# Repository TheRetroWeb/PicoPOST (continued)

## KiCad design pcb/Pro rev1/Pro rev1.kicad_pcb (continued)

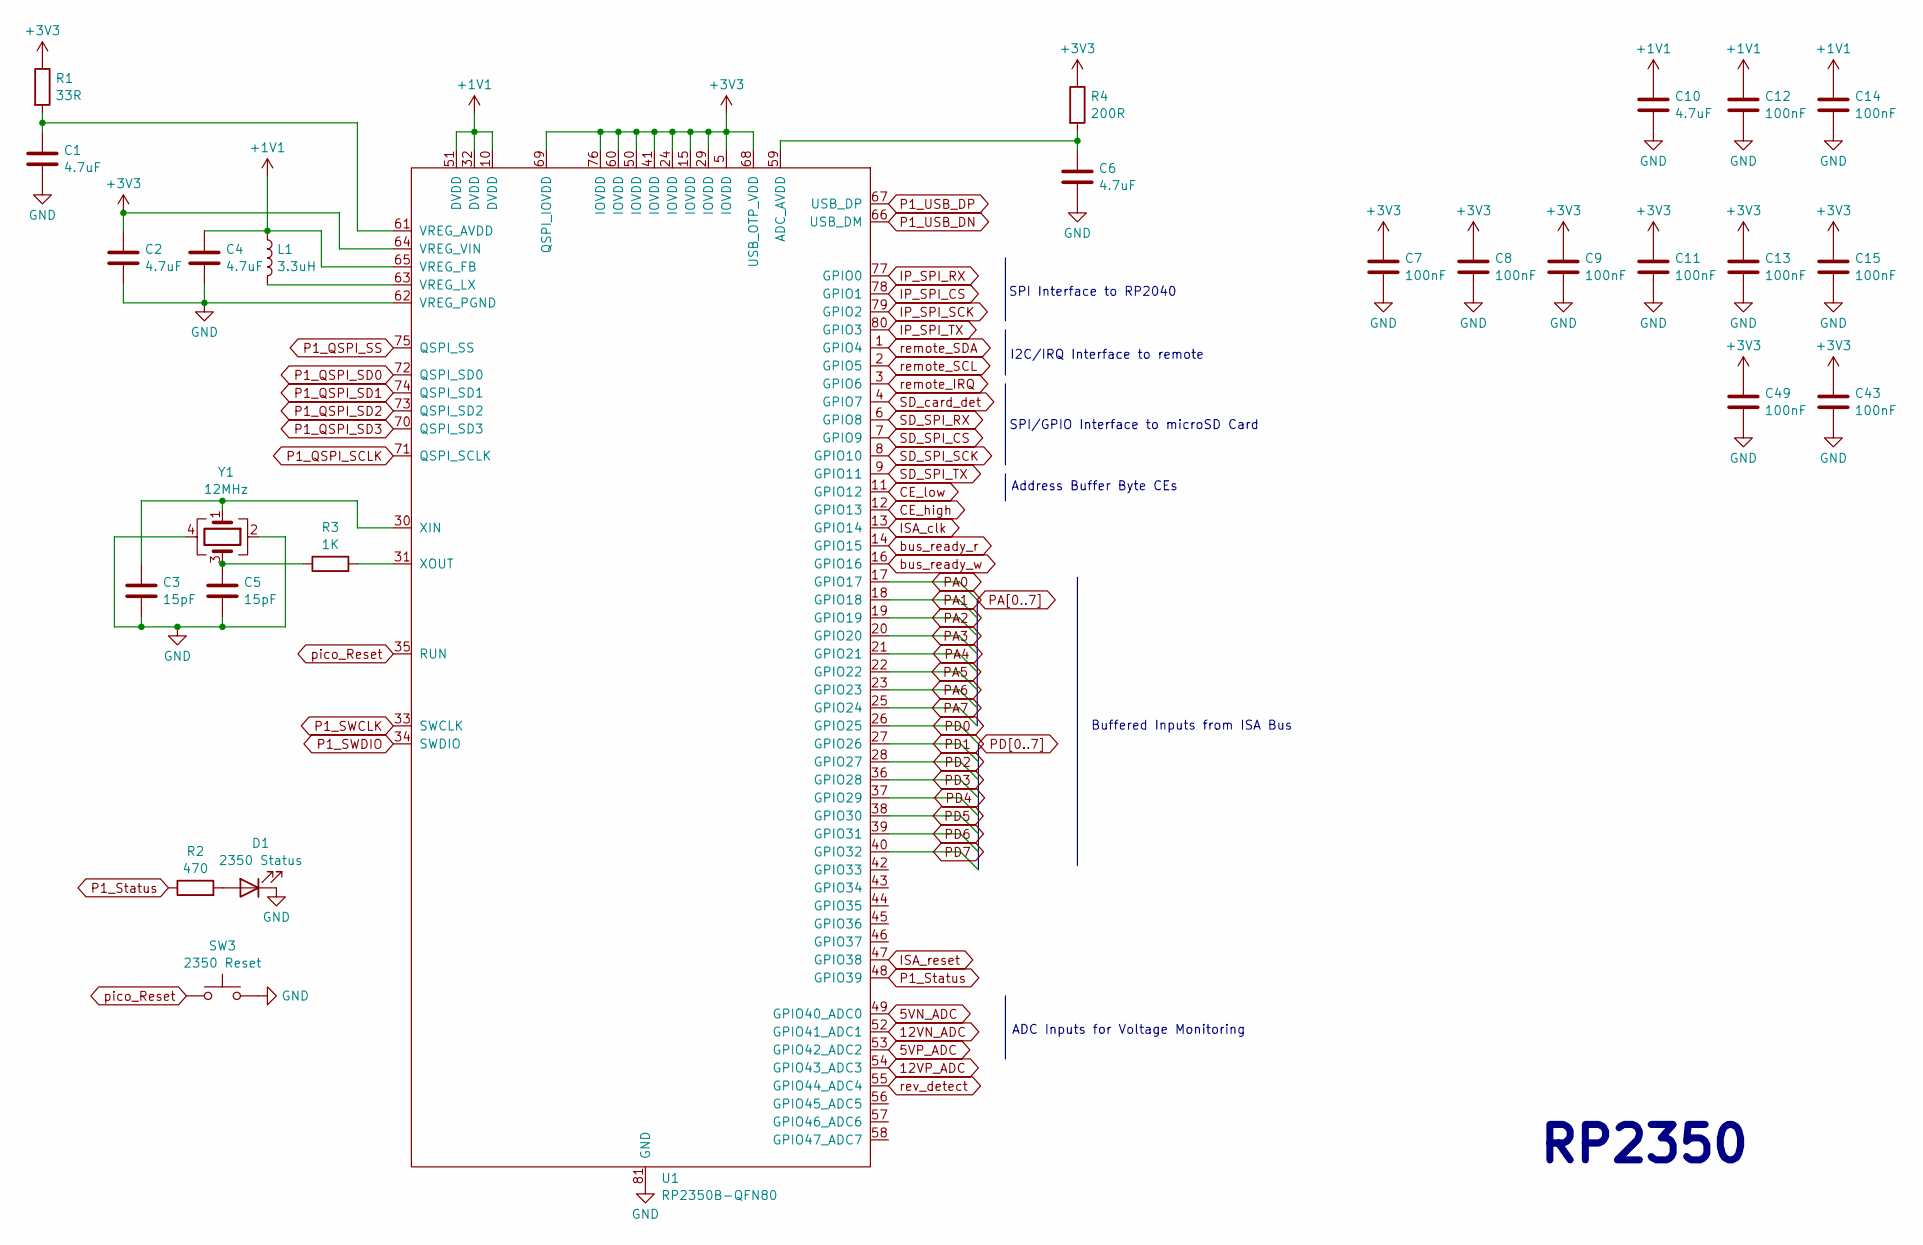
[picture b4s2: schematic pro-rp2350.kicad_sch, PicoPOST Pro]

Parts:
C1, C2, C4: 4.7uF; C_0402_1005Metric
C3, C5: 15pF; C_0402_1005Metric
C6, C10: 4.7uF; C_0603_1608Metric
C7, C8, C9, C11, C12, C13, C14, C15, C43, C49: 100nF; C_0402_1005Metric
D1: 2350 Status; LED_0805_2012Metric
L1: 3.3uH; L_Murata_DFE201610P
R1: 33R; R_0402_1005Metric
R2: 470; R_0603_1608Metric
R3: 1K; R_0402_1005Metric
R4: 200R; R_0402_1005Metric
SW3: 2350 Reset; SW_SPST_TS-1088-xR020
U1: RP2350B-QFN80; RP2350B_QFN-80_EP_10.573x10.573_Pitch0.4mm
Y1: 12MHz; Crystal_SMD_Abracon_ABM8G-4Pin_3.2x2.5mm

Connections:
5VN_ADC: U1.49 (GPIO40_ADC0); also elsewhere on the board
5VP_ADC: U1.53 (GPIO42_ADC2); also elsewhere on the board
12VN_ADC: U1.52 (GPIO41_ADC1); also elsewhere on the board
12VP_ADC: U1.54 (GPIO43_ADC3); also elsewhere on the board
+1V1: C4.1, C10.1, C12.1, C14.1, L1.1, U1.10 (DVDD), U1.32 (DVDD), U1.51 (DVDD), U1.65 (VREG_FB)
+3V3: C2.1, C7.1, C8.1, C9.1, C11.1, C13.1, C15.1, C43.1, C49.1, R1.1, R4.1, U1.5 (IOVDD), U1.15 (IOVDD), U1.24 (IOVDD), U1.29 (IOVDD), U1.41 (IOVDD), U1.50 (IOVDD), U1.60 (IOVDD), U1.64 (VREG_VIN), U1.68 (USB_OTP_VDD), U1.69 (QSPI_IOVDD), U1.76 (IOVDD); also elsewhere on the board
CE_high: U1.12 (GPIO13); also elsewhere on the board
CE_low: U1.11 (GPIO12); also elsewhere on the board
GND: C1.2, C2.2, C3.1, C4.2, C5.2, C6.2, C7.2, C8.2, C9.2, C10.2, C11.2, C12.2, C13.2, C14.2, C15.2, C43.2, C49.2, D1.1 (K), SW3.2, U1.62 (VREG_PGND), U1.81 (GND), Y1.2, Y1.4; also elsewhere on the board
IP_SPI_CS: U1.78 (GPIO1); also elsewhere on the board
IP_SPI_RX: U1.77 (GPIO0); also elsewhere on the board
IP_SPI_SCK: U1.79 (GPIO2); also elsewhere on the board
IP_SPI_TX: U1.80 (GPIO3); also elsewhere on the board
ISA_clk: U1.13 (GPIO14); also elsewhere on the board
ISA_reset: U1.47 (GPIO38); also elsewhere on the board
unnamed: C5.1, R3.1, Y1.3
unnamed: D1.2 (A), R2.2
unnamed: C6.1, R4.2, U1.59 (ADC_AVDD)
unnamed: C1.1, R1.2, U1.61 (VREG_AVDD)
unnamed: L1.2, U1.63 (VREG_LX)
unnamed: C3.2, U1.30 (XIN), Y1.1
unnamed: R3.2, U1.31 (XOUT)
P1_QSPI_SCLK: U1.71 (QSPI_SCLK); also elsewhere on the board
P1_QSPI_SD0: U1.72 (QSPI_SD0); also elsewhere on the board
P1_QSPI_SD1: U1.74 (QSPI_SD1); also elsewhere on the board
P1_QSPI_SD2: U1.73 (QSPI_SD2); also elsewhere on the board
P1_QSPI_SD3: U1.70 (QSPI_SD3); also elsewhere on the board
P1_QSPI_SS: U1.75 (QSPI_SS); also elsewhere on the board
P1_SWCLK: U1.33 (SWCLK); also elsewhere on the board
P1_SWDIO: U1.34 (SWDIO); also elsewhere on the board
P1_Status: R2.1, U1.48 (GPIO39)
P1_USB_DN: U1.66 (USB_DM); also elsewhere on the board
P1_USB_DP: U1.67 (USB_DP); also elsewhere on the board
PA0: U1.17 (GPIO17); also elsewhere on the board
PA1: U1.18 (GPIO18); also elsewhere on the board
PA2: U1.19 (GPIO19); also elsewhere on the board
PA3: U1.20 (GPIO20); also elsewhere on the board
PA4: U1.21 (GPIO21); also elsewhere on the board
PA5: U1.22 (GPIO22); also elsewhere on the board
PA6: U1.23 (GPIO23); also elsewhere on the board
PA7: U1.25 (GPIO24); also elsewhere on the board
PD0: U1.26 (GPIO25); also elsewhere on the board
PD1: U1.27 (GPIO26); also elsewhere on the board
PD2: U1.28 (GPIO27); also elsewhere on the board
PD3: U1.36 (GPIO28); also elsewhere on the board
PD4: U1.37 (GPIO29); also elsewhere on the board
PD5: U1.38 (GPIO30); also elsewhere on the board
PD6: U1.39 (GPIO31); also elsewhere on the board
PD7: U1.40 (GPIO32); also elsewhere on the board
SD_SPI_CS: U1.7 (GPIO9); also elsewhere on the board
SD_SPI_RX: U1.6 (GPIO8); also elsewhere on the board
SD_SPI_SCK: U1.8 (GPIO10); also elsewhere on the board
SD_SPI_TX: U1.9 (GPIO11); also elsewhere on the board
SD_card_det: U1.4 (GPIO7); also elsewhere on the board
bus_ready_r: U1.14 (GPIO15); also elsewhere on the board
bus_ready_w: U1.16 (GPIO16); also elsewhere on the board
pico_Reset: SW3.1, U1.35 (RUN)
remote_IRQ: U1.3 (GPIO6); also elsewhere on the board
remote_SCL: U1.2 (GPIO5); also elsewhere on the board
remote_SDA: U1.1 (GPIO4); also elsewhere on the board
rev_detect: U1.55 (GPIO44_ADC4); also elsewhere on the board

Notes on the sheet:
SPI/GPIO Interface to microSD Card
I2C/IRQ Interface to remote
Buffered Inputs from ISA Bus
SPI Interface to RP2040
Address Buffer Byte CEs
ADC Inputs for Voltage Monitoring
RP2350

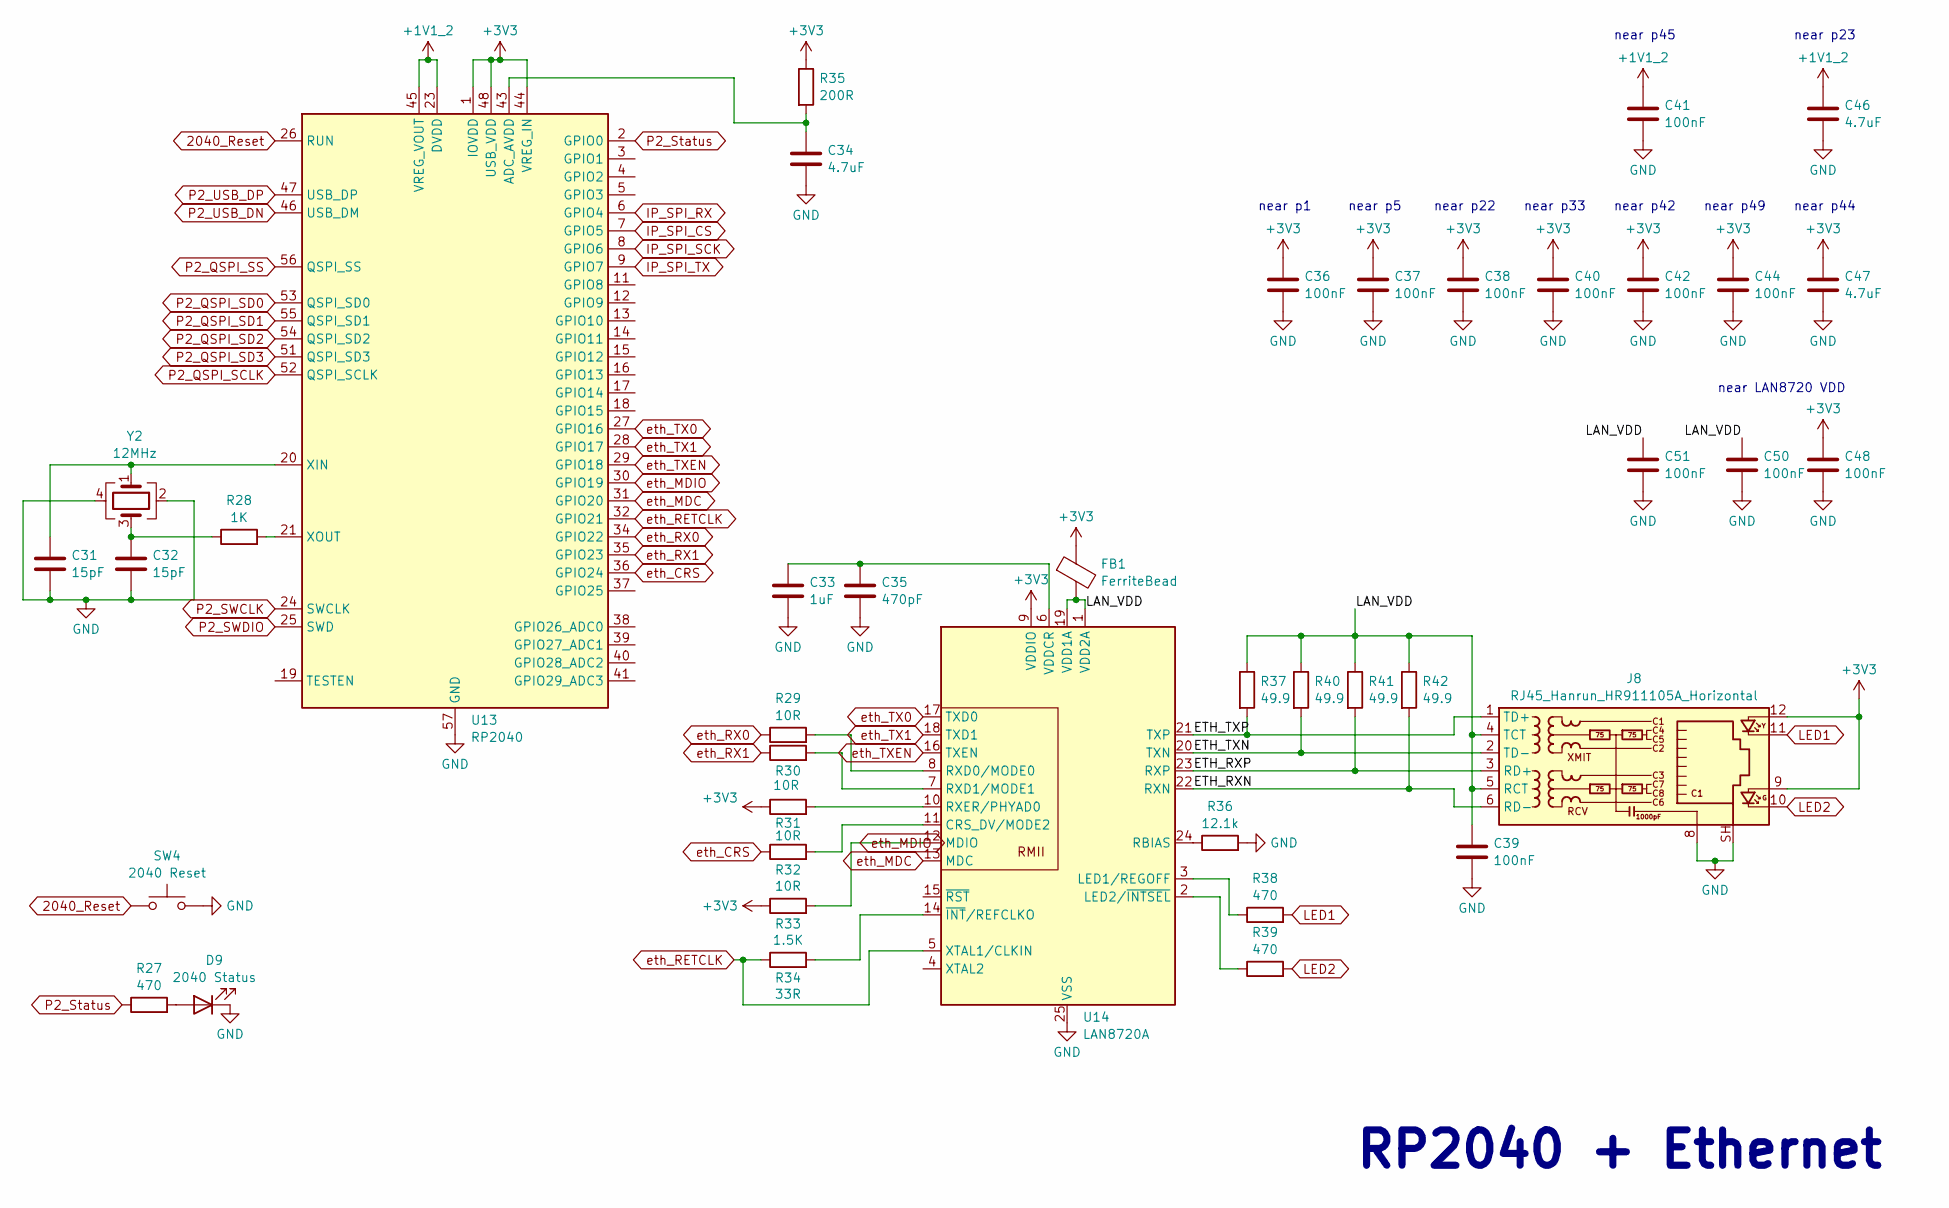
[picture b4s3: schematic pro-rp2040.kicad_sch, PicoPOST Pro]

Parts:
C31, C32: 15pF; C_0402_1005Metric
C33: 1uF; C_0603_1608Metric
C34, C46, C47: 4.7uF; C_0603_1608Metric
C35: 470pF; C_0603_1608Metric
C36, C37, C38, C39, C40, C41, C42, C44, C48, C50, C51: 100nF; C_0402_1005Metric
D9: 2040 Status; LED_0805_2012Metric
FB1: FerriteBead; L_0603_1608Metric
J8: RJ45_Hanrun_HR911105A_Horizontal
R27, R38, R39: 470; R_0603_1608Metric
R28: 1K; R_0402_1005Metric
R29, R30, R31, R32: 10R; R_0402_1005Metric
R33: 1.5K; R_0402_1005Metric
R34: 33R; R_0402_1005Metric
R35: 200R; R_0402_1005Metric
R36: 12.1k; R_0402_1005Metric
R37, R40, R41, R42: 49.9; R_0603_1608Metric
SW4: 2040 Reset; SW_SPST_TS-1088-xR020
U13: RP2040; QFN-56-1EP_7x7mm_P0.4mm_EP3.2x3.2mm
U14: LAN8720A; VQFN-24-1EP_4x4mm_P0.5mm_EP2.5x2.5mm_ThermalVias
Y2: 12MHz; Crystal_SMD_Abracon_ABM8G-4Pin_3.2x2.5mm

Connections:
2040_Reset: SW4.1, U13.26 (RUN)
+1V1_2: C41.1, C46.1, U13.23 (DVDD), U13.45 (VREG_VOUT), U13.50 (DVDD)
+3V3: C36.1, C37.1, C38.1, C40.1, C42.1, C44.1, C47.1, C48.1, FB1.1, J8.9, J8.12, R31.1, R33.1, R35.1, U13.1 (IOVDD), U13.10 (IOVDD), U13.22 (IOVDD), U13.33 (IOVDD), U13.42 (IOVDD), U13.44 (VREG_IN), U13.48 (USB_VDD), U13.49 (IOVDD), U14.9 (VDDIO); also elsewhere on the board
/RP2040/ETH_RXN: J8.6 (RD-), R42.2, U14.22 (RXN)
/RP2040/ETH_RXP: J8.3 (RD+), R41.2, U14.23 (RXP)
/RP2040/ETH_TXN: J8.2 (TD-), R40.2, U14.20 (TXN)
/RP2040/ETH_TXP: J8.1 (TD+), R37.2, U14.21 (TXP)
/RP2040/LAN_VDD: C39.1, C50.1, C51.1, FB1.2, J8.4 (TCT), J8.5 (RCT), R37.1, R40.1, R41.1, R42.1, U14.1 (VDD2A), U14.19 (VDD1A)
GND: C31.1, C32.2, C33.2, C34.2, C35.2, C36.2, C37.2, C38.2, C39.2, C40.2, C41.2, C42.2, C44.2, C46.2, C47.2, C48.2, C50.2, C51.2, D9.1 (K), J8.8, J8.SH, R36.2, SW4.2, U13.57 (GND), U14.25 (VSS), Y2.2, Y2.4; also elsewhere on the board
IP_SPI_CS: U13.7 (GPIO5); also elsewhere on the board
IP_SPI_RX: U13.6 (GPIO4); also elsewhere on the board
IP_SPI_SCK: U13.8 (GPIO6); also elsewhere on the board
IP_SPI_TX: U13.9 (GPIO7); also elsewhere on the board
LED1: J8.11, R38.2
LED2: J8.10, R39.2
unnamed: C32.1, R28.1, Y2.3
unnamed: D9.2 (A), R27.2
unnamed: C34.1, R35.2, U13.43 (ADC_AVDD)
unnamed: C31.2, U13.20 (XIN), Y2.1
unnamed: R28.2, U13.21 (XOUT)
unnamed: R32.2, U14.11 (CRS_DV/MODE2)
unnamed: R38.1, U14.3 (LED1/REGOFF)
unnamed: R39.1, U14.2 (LED2/~INTSEL)
unnamed: R36.1, U14.24 (RBIAS)
unnamed: R29.2, U14.8 (RXD0/MODE0)
unnamed: R30.2, U14.7 (RXD1/MODE1)
unnamed: R31.2, U14.10 (RXER/PHYAD0)
unnamed: C33.1, C35.1, U14.6 (VDDCR)
unnamed: R34.2, U14.14 (~INT/REFCLKO)
P2_QSPI_SCLK: U13.52 (QSPI_SCLK); also elsewhere on the board
P2_QSPI_SD0: U13.53 (QSPI_SD0); also elsewhere on the board
P2_QSPI_SD1: U13.55 (QSPI_SD1); also elsewhere on the board
P2_QSPI_SD2: U13.54 (QSPI_SD2); also elsewhere on the board
P2_QSPI_SD3: U13.51 (QSPI_SD3); also elsewhere on the board
P2_QSPI_SS: U13.56 (QSPI_SS); also elsewhere on the board
P2_SWCLK: U13.24 (SWCLK); also elsewhere on the board
P2_SWDIO: U13.25 (SWD); also elsewhere on the board
P2_Status: R27.1, U13.2 (GPIO0)
P2_USB_DN: U13.46 (USB_DM); also elsewhere on the board
P2_USB_DP: U13.47 (USB_DP); also elsewhere on the board
eth_CRS: R32.1, U13.36 (GPIO24)
eth_MDC: U13.31 (GPIO20), U14.13 (MDC)
eth_MDIO: R33.2, U13.30 (GPIO19), U14.12 (MDIO)
eth_RETCLK: R34.1, U13.32 (GPIO21), U14.5 (XTAL1/CLKIN)
eth_RX0: R29.1, U13.34 (GPIO22)
eth_RX1: R30.1, U13.35 (GPIO23)
eth_TX0: U13.27 (GPIO16), U14.17 (TXD0)
eth_TX1: U13.28 (GPIO17), U14.18 (TXD1)
eth_TXEN: U13.29 (GPIO18), U14.16 (TXEN)

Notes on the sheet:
near p42
near p5
near p44
near p22
near LAN8720 VDD
near p1
near p49
near p45
near p23
near p33
RP2040 + Ethernet

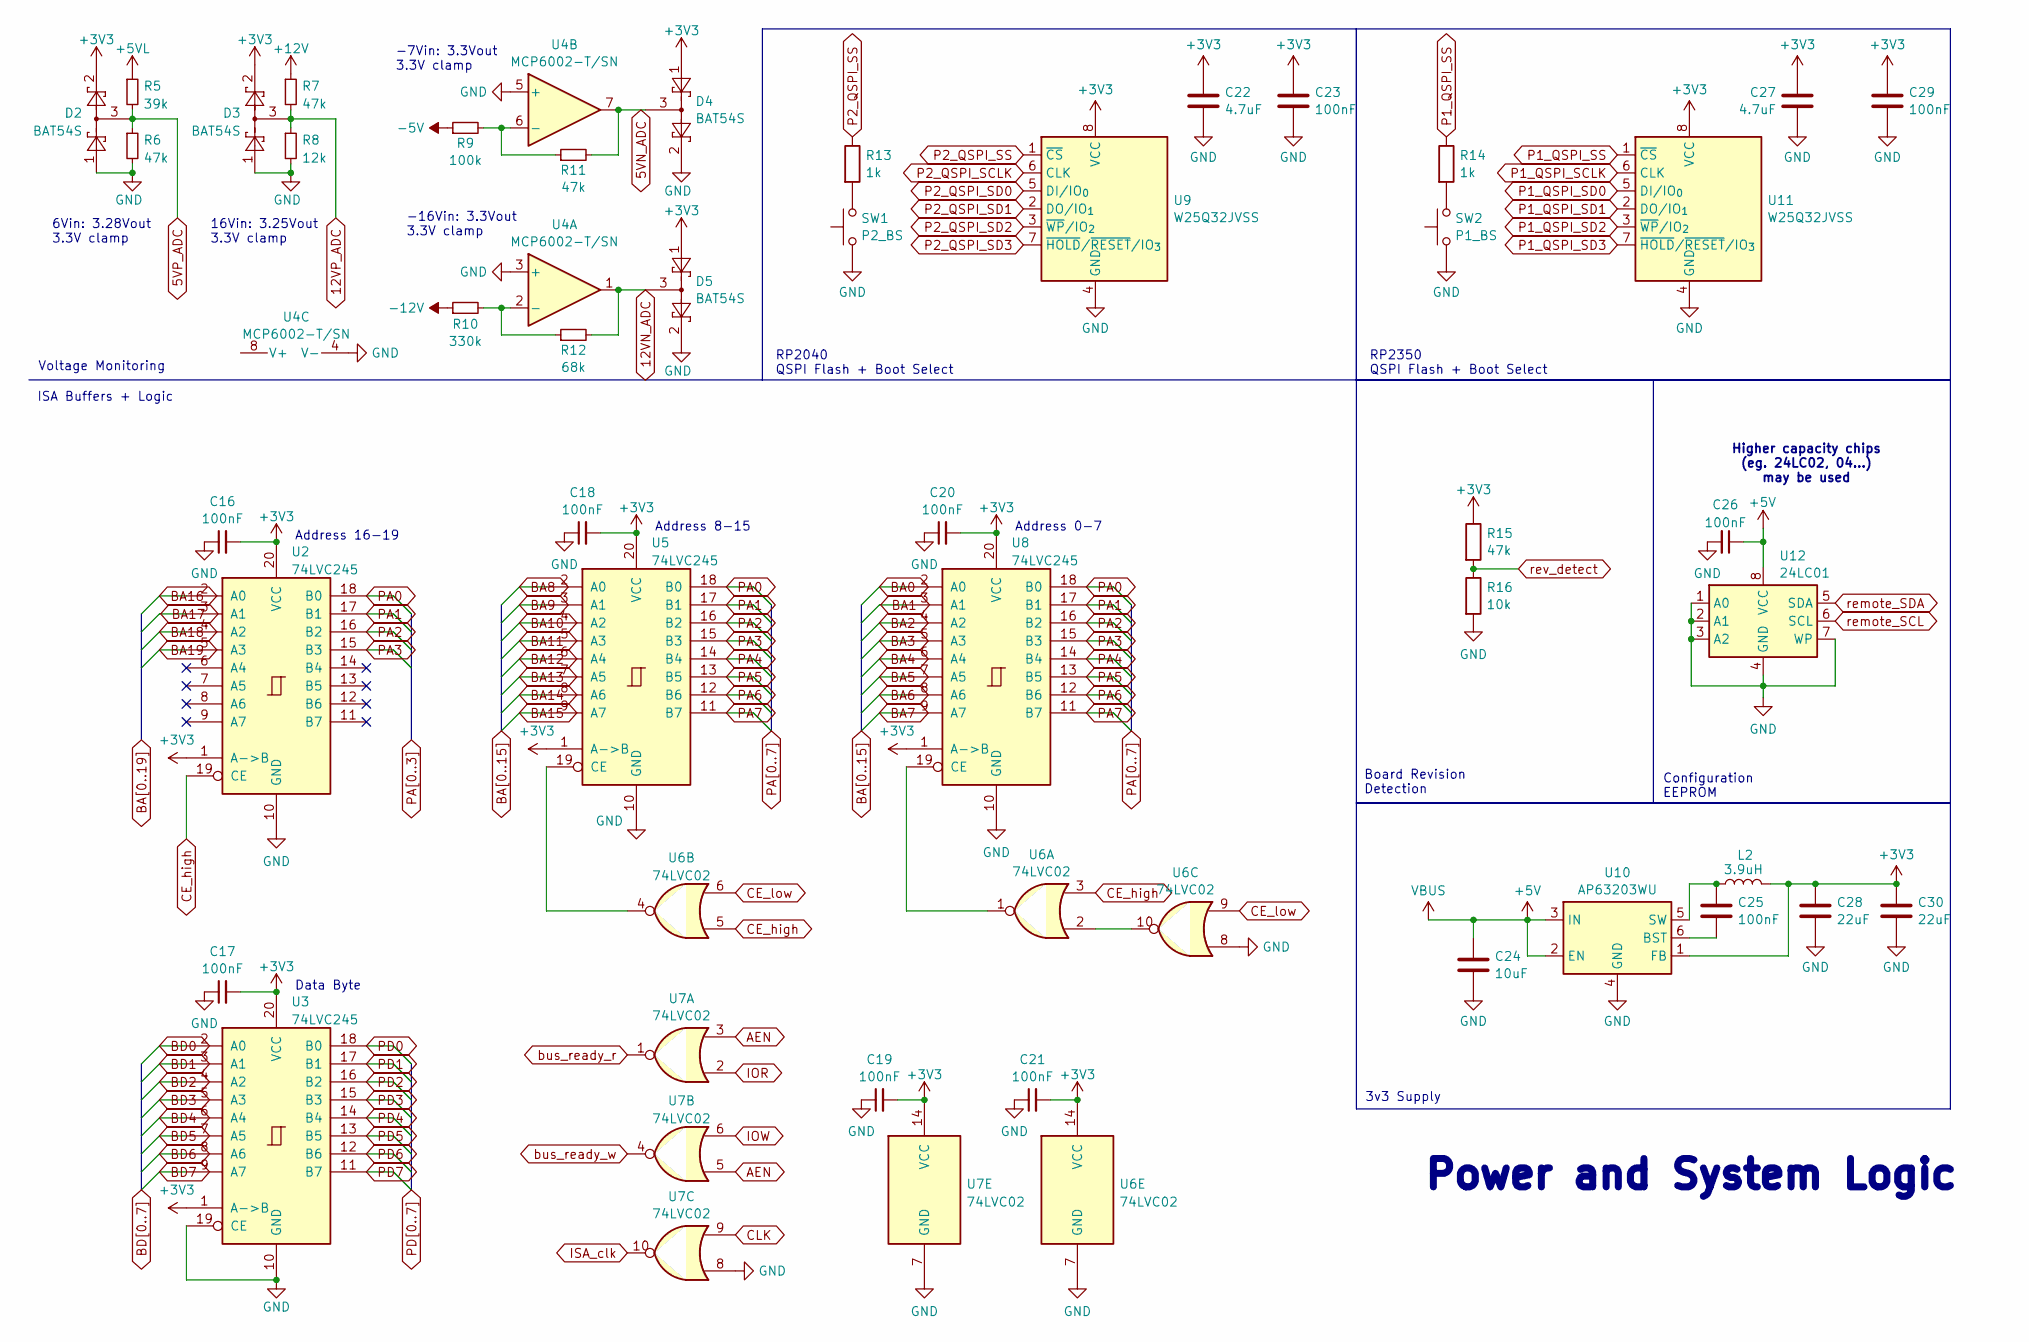
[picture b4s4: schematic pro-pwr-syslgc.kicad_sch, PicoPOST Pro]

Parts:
C16, C17, C18, C19, C20, C21, C23, C25, C26, C29: 100nF; C_0402_1005Metric
C22, C27: 4.7uF; C_0603_1608Metric
C24: 10uF; C_0805_2012Metric
C28, C30: 22uF; C_1206_3216Metric
D2, D3, D4, D5: BAT54S; SOT-23_Handsoldering
L2: 3.9uH; L_APV_ANR4030
R5: 39k; R_0603_1608Metric
R6, R7, R11, R15: 47k; R_0603_1608Metric
R8: 12k; R_0603_1608Metric
R9: 100k; R_0603_1608Metric
R10: 330k; R_0603_1608Metric
R12: 68k; R_0603_1608Metric
R13, R14: 1k; R_0603_1608Metric
R16: 10k; R_0603_1608Metric
SW1: P2_BS; SW_SPST_TS-1088-xR020
SW2: P1_BS; SW_SPST_TS-1088-xR020
U2, U3, U5, U8: 74LVC245; TSSOP-20_4.4x6.5mm_P0.65mm
U4: MCP6002-T/SN; SOIC-8_3.9x4.9mm_P1.27mm
U6, U7: 74LVC02; TSSOP-14_4.4x5mm_P0.65mm
U9, U11: W25Q32JVSS; SOIC-8_5.3x5.3mm_P1.27mm
U10: AP63203WU; TSOT-23-6
U12: 24LC01; SOIC-8_3.9x4.9mm_P1.27mm

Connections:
5VN_ADC: D4.3, R11.2, U4.7; also elsewhere on the board
5VP_ADC: D2.3, R5.2, R6.1; also elsewhere on the board
12VN_ADC: D5.3, R12.2, U4.1; also elsewhere on the board
12VP_ADC: D3.3, R7.2, R8.1; also elsewhere on the board
+3V3: C16.2, C17.2, C18.2, C19.2, C20.2, C21.2, C22.1, C23.1, C27.1, C28.1, C29.1, C30.1, D2.2, D3.2, D4.1, D5.1, L2.2, R15.1, U2.1 (A->B), U2.20 (VCC), U3.1 (A->B), U3.20 (VCC), U5.1 (A->B), U5.20 (VCC), U6.14 (VCC), U7.14 (VCC), U8.1 (A->B), U8.20 (VCC), U9.8 (VCC), U10.1 (FB), U11.8 (VCC); also elsewhere on the board
+5V: C24.1, C26.1, U10.2 (EN), U10.3 (IN), U12.8 (VCC); also elsewhere on the board
+5VL: R5.1; also elsewhere on the board
+12V: R7.1; also elsewhere on the board
-5V: R9.1; also elsewhere on the board
-12V: R10.1; also elsewhere on the board
AEN: U7.3, U7.5; also elsewhere on the board
BA0: U8.2 (A0); also elsewhere on the board
BA1: U8.3 (A1); also elsewhere on the board
BA2: U8.4 (A2); also elsewhere on the board
BA3: U8.5 (A3); also elsewhere on the board
BA4: U8.6 (A4); also elsewhere on the board
BA5: U8.7 (A5); also elsewhere on the board
BA6: U8.8 (A6); also elsewhere on the board
BA7: U8.9 (A7); also elsewhere on the board
BA8: U5.2 (A0); also elsewhere on the board
BA9: U5.3 (A1); also elsewhere on the board
BA10: U5.4 (A2); also elsewhere on the board
BA11: U5.5 (A3); also elsewhere on the board
BA12: U5.6 (A4); also elsewhere on the board
BA13: U5.7 (A5); also elsewhere on the board
BA14: U5.8 (A6); also elsewhere on the board
BA15: U5.9 (A7); also elsewhere on the board
BA16: U2.2 (A0); also elsewhere on the board
BA17: U2.3 (A1); also elsewhere on the board
BA18: U2.4 (A2); also elsewhere on the board
BA19: U2.5 (A3); also elsewhere on the board
BD0: U3.2 (A0); also elsewhere on the board
BD1: U3.3 (A1); also elsewhere on the board
BD2: U3.4 (A2); also elsewhere on the board
BD3: U3.5 (A3); also elsewhere on the board
BD4: U3.6 (A4); also elsewhere on the board
BD5: U3.7 (A5); also elsewhere on the board
BD6: U3.8 (A6); also elsewhere on the board
BD7: U3.9 (A7); also elsewhere on the board
CE_high: U2.19 (CE), U6.3, U6.5; also elsewhere on the board
CE_low: U6.6, U6.9; also elsewhere on the board
CLK: U7.9; also elsewhere on the board
GND: C16.1, C17.1, C18.1, C19.1, C20.1, C21.1, C22.2, C23.2, C24.2, C26.2, C27.2, C28.2, C29.2, C30.2, D2.1, D3.1, D4.2, D5.2, R6.2, R8.2, R16.2, SW1.1, SW2.1, U2.10 (GND), U3.10 (GND), U3.19 (CE), U4.3 (+), U4.4 (V-), U4.5 (+), U5.10 (GND), U6.7 (GND), U6.8, U7.7 (GND), U7.8, U8.10 (GND), U9.4 (GND), U10.4 (GND), U11.4 (GND), U12.1 (A0), U12.2 (A1), U12.3 (A2), U12.4 (GND), U12.7 (WP); also elsewhere on the board
IOR: U7.2; also elsewhere on the board
IOW: U7.6; also elsewhere on the board
ISA_clk: U7.10; also elsewhere on the board
unnamed: R13.2, SW1.2
unnamed: R14.2, SW2.2
unnamed: R10.2, R12.1, U4.2 (-)
unnamed: R9.2, R11.1, U4.6 (-)
unnamed: U5.19 (CE), U6.4
unnamed: U6.2, U6.10
unnamed: U6.1, U8.19 (CE)
unnamed: C25.2, U10.6 (BST)
unnamed: C25.1, L2.1, U10.5 (SW)
P1_QSPI_SCLK: U11.6 (CLK); also elsewhere on the board
P1_QSPI_SD0: U11.5 (DI/IO_{0}); also elsewhere on the board
P1_QSPI_SD1: U11.2 (DO/IO_{1}); also elsewhere on the board
P1_QSPI_SD2: U11.3 (~WP/IO_{2}); also elsewhere on the board
P1_QSPI_SD3: U11.7 (~HOLD/~RESET/IO_{3}); also elsewhere on the board
P1_QSPI_SS: R14.1, U11.1 (~CS); also elsewhere on the board
P2_QSPI_SCLK: U9.6 (CLK); also elsewhere on the board
P2_QSPI_SD0: U9.5 (DI/IO_{0}); also elsewhere on the board
P2_QSPI_SD1: U9.2 (DO/IO_{1}); also elsewhere on the board
P2_QSPI_SD2: U9.3 (~WP/IO_{2}); also elsewhere on the board
P2_QSPI_SD3: U9.7 (~HOLD/~RESET/IO_{3}); also elsewhere on the board
P2_QSPI_SS: R13.1, U9.1 (~CS); also elsewhere on the board
PA0: U2.18 (B0), U5.18 (B0), U8.18 (B0); also elsewhere on the board
PA1: U2.17 (B1), U5.17 (B1), U8.17 (B1); also elsewhere on the board
PA2: U2.16 (B2), U5.16 (B2), U8.16 (B2); also elsewhere on the board
PA3: U2.15 (B3), U5.15 (B3), U8.15 (B3); also elsewhere on the board
PA4: U5.14 (B4), U8.14 (B4); also elsewhere on the board
PA5: U5.13 (B5), U8.13 (B5); also elsewhere on the board
PA6: U5.12 (B6), U8.12 (B6); also elsewhere on the board
PA7: U5.11 (B7), U8.11 (B7); also elsewhere on the board
PD0: U3.18 (B0); also elsewhere on the board
PD1: U3.17 (B1); also elsewhere on the board
PD2: U3.16 (B2); also elsewhere on the board
PD3: U3.15 (B3); also elsewhere on the board
PD4: U3.14 (B4); also elsewhere on the board
PD5: U3.13 (B5); also elsewhere on the board
PD6: U3.12 (B6); also elsewhere on the board
PD7: U3.11 (B7); also elsewhere on the board
bus_ready_r: U7.1; also elsewhere on the board
bus_ready_w: U7.4; also elsewhere on the board
remote_SCL: U12.6 (SCL); also elsewhere on the board
remote_SDA: U12.5 (SDA); also elsewhere on the board
rev_detect: R15.2, R16.1; also elsewhere on the board

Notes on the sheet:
RP2350 QSPI Flash + Boot Select
Higher capacity chips (eg. 24LC02, 04...) may be used
Voltage Monitoring
Address 0-7
ISA Buffers + Logic
Data Byte
-16Vin: 3.3Vout 3.3V clamp
Address 16-19
Power and System Logic
3v3 Supply
Board Revision Detection
Address 8-15
-7Vin: 3.3Vout 3.3V clamp
Configuration EEPROM
RP2040 QSPI Flash + Boot Select
16Vin: 3.25Vout 3.3V clamp
6Vin: 3.28Vout 3.3V clamp

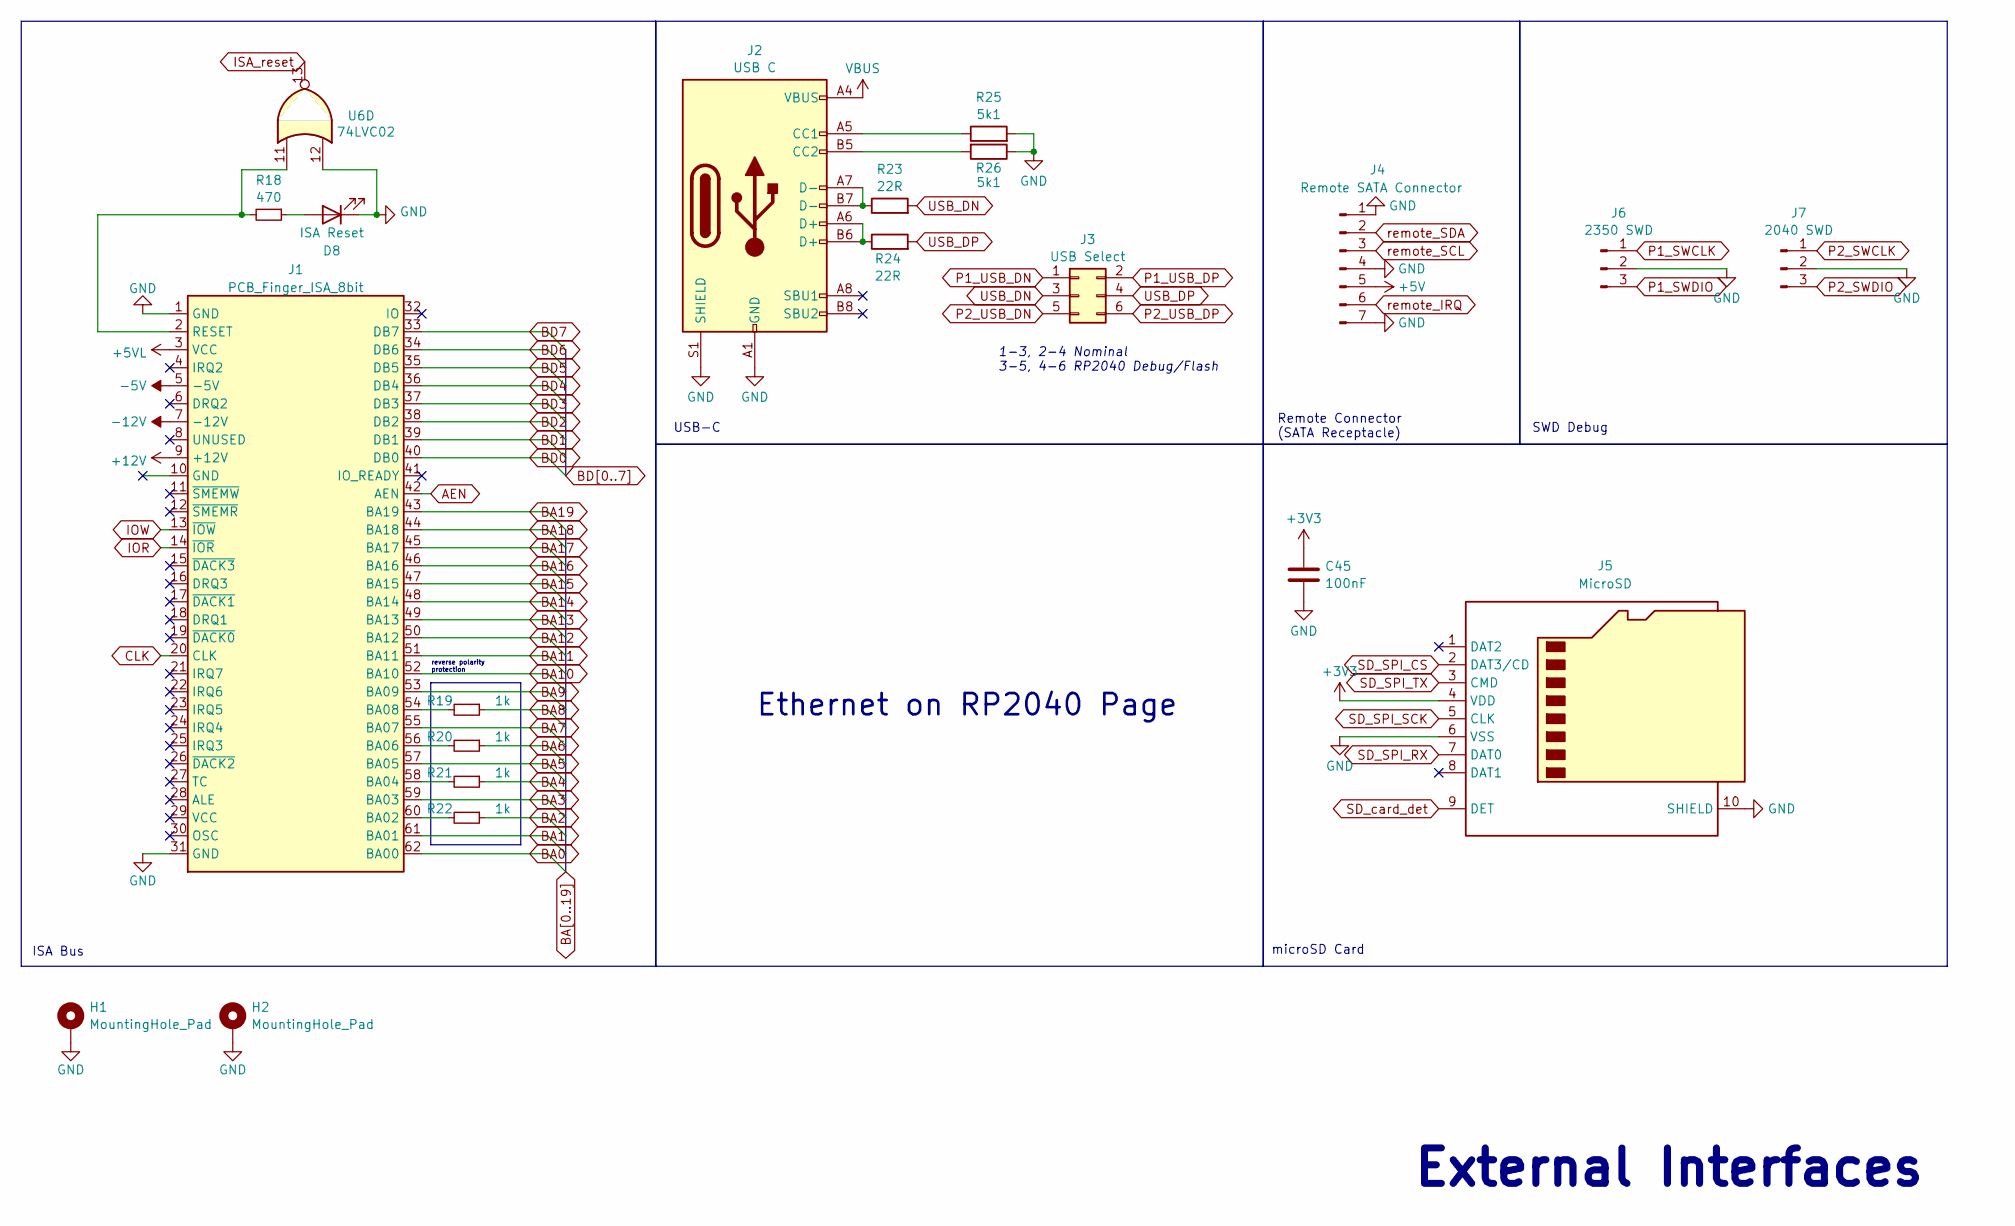
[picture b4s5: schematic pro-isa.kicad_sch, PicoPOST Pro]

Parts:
C45: 100nF; C_0402_1005Metric
D8: ISA Reset; LED_0805_2012Metric
H1, H2: MountingHole_Pad; MountingHole_3.2mm_M3_Pad
J1: PCB_Finger_ISA_8bit; BUS_IDE8
J2: USB C; USB_C_Receptacle_G-Switch_GT-USB-7010ASV
J3: USB Select; PinHeader_2x03_P2.54mm_Vertical
J4: Remote SATA Connector; Molex-47080-4001-0-0-0
J5: MicroSD; TF-SMD_TF-PUSH
J6: 2350 SWD; PinHeader_1x03_P2.54mm_Vertical
J7: 2040 SWD; PinHeader_1x03_P2.54mm_Vertical
R18: 470; R_0603_1608Metric
R19, R20, R21, R22: 1k; R_0603_1608Metric
R23, R24: 22R; R_0603_1608Metric
R25, R26: 5k1; R_0603_1608Metric
U6: 74LVC02; TSSOP-14_4.4x5mm_P0.65mm

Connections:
+3V3: C45.1, J5.4 (VDD); also elsewhere on the board
+5V: J2.A4 (VBUS), J2.A9 (VBUS), J2.B4 (VBUS), J2.B9 (VBUS), J4.5; also elsewhere on the board
+5VL: J1.3 (VCC); also elsewhere on the board
+12V: J1.9 (+12V); also elsewhere on the board
-5V: J1.5 (-5V); also elsewhere on the board
-12V: J1.7 (-12V); also elsewhere on the board
AEN: J1.42 (AEN); also elsewhere on the board
BA0: J1.62 (BA00); also elsewhere on the board
BA1: J1.61 (BA01); also elsewhere on the board
BA2: R22.1; also elsewhere on the board
BA3: J1.59 (BA03); also elsewhere on the board
BA4: R21.1; also elsewhere on the board
BA5: J1.57 (BA05); also elsewhere on the board
BA6: R20.1; also elsewhere on the board
BA7: J1.55 (BA07); also elsewhere on the board
BA8: R19.1; also elsewhere on the board
BA9: J1.53 (BA09); also elsewhere on the board
BA10: J1.52 (BA10); also elsewhere on the board
BA11: J1.51 (BA11); also elsewhere on the board
BA12: J1.50 (BA12); also elsewhere on the board
BA13: J1.49 (BA13); also elsewhere on the board
BA14: J1.48 (BA14); also elsewhere on the board
BA15: J1.47 (BA15); also elsewhere on the board
BA16: J1.46 (BA16); also elsewhere on the board
BA17: J1.45 (BA17); also elsewhere on the board
BA18: J1.44 (BA18); also elsewhere on the board
BA19: J1.43 (BA19); also elsewhere on the board
BD0: J1.40 (DB0); also elsewhere on the board
BD1: J1.39 (DB1); also elsewhere on the board
BD2: J1.38 (DB2); also elsewhere on the board
BD3: J1.37 (DB3); also elsewhere on the board
BD4: J1.36 (DB4); also elsewhere on the board
BD5: J1.35 (DB5); also elsewhere on the board
BD6: J1.34 (DB6); also elsewhere on the board
BD7: J1.33 (DB7); also elsewhere on the board
CLK: J1.20 (CLK); also elsewhere on the board
GND: C45.2, D8.1 (K), H1.1, H2.1, J1.1 (GND), J1.31 (GND), J2.A1 (GND), J2.A12 (GND), J2.B1 (GND), J2.B12 (GND), J2.S1 (SHIELD), J4.1, J4.4, J4.7, J5.6 (VSS), J5.10 (SHIELD), J6.2, J7.2, R25.2, R26.1, U6.12; also elsewhere on the board
IOR: J1.14 (~IOR); also elsewhere on the board
IOW: J1.13 (~IOW); also elsewhere on the board
ISA_reset: U6.13; also elsewhere on the board
unnamed: D8.2 (A), R18.1
unnamed: J1.60 (BA02), R22.2
unnamed: J1.58 (BA04), R21.2
unnamed: J1.56 (BA06), R20.2
unnamed: J1.54 (BA08), R19.2
unnamed: J1.2 (RESET), R18.2, U6.11
unnamed: J2.A5 (CC1), R25.1
unnamed: J2.B5 (CC2), R26.2
unnamed: J2.A6 (D+), J2.B6 (D+), R24.1
unnamed: J2.A7 (D-), J2.B7 (D-), R23.1
P1_SWCLK: J6.1; also elsewhere on the board
P1_SWDIO: J6.3; also elsewhere on the board
P1_USB_DN: J3.1; also elsewhere on the board
P1_USB_DP: J3.2; also elsewhere on the board
P2_SWCLK: J7.1; also elsewhere on the board
P2_SWDIO: J7.3; also elsewhere on the board
P2_USB_DN: J3.5; also elsewhere on the board
P2_USB_DP: J3.6; also elsewhere on the board
SD_SPI_CS: J5.2 (DAT3/CD); also elsewhere on the board
SD_SPI_RX: J5.7 (DAT0); also elsewhere on the board
SD_SPI_SCK: J5.5 (CLK); also elsewhere on the board
SD_SPI_TX: J5.3 (CMD); also elsewhere on the board
SD_card_det: J5.9 (DET); also elsewhere on the board
USB_DN: J3.3, R23.2
USB_DP: J3.4, R24.2
remote_IRQ: J4.6; also elsewhere on the board
remote_SCL: J4.3; also elsewhere on the board
remote_SDA: J4.2; also elsewhere on the board

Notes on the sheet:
microSD Card
1-3, 2-4 Nominal 3-5, 4-6 RP2040 Debug/Flash
USB-C
Remote Connector (SATA Receptacle)
ISA Bus
SWD Debug
Ethernet on RP2040 Page
reverse polarity protection
External Interfaces
